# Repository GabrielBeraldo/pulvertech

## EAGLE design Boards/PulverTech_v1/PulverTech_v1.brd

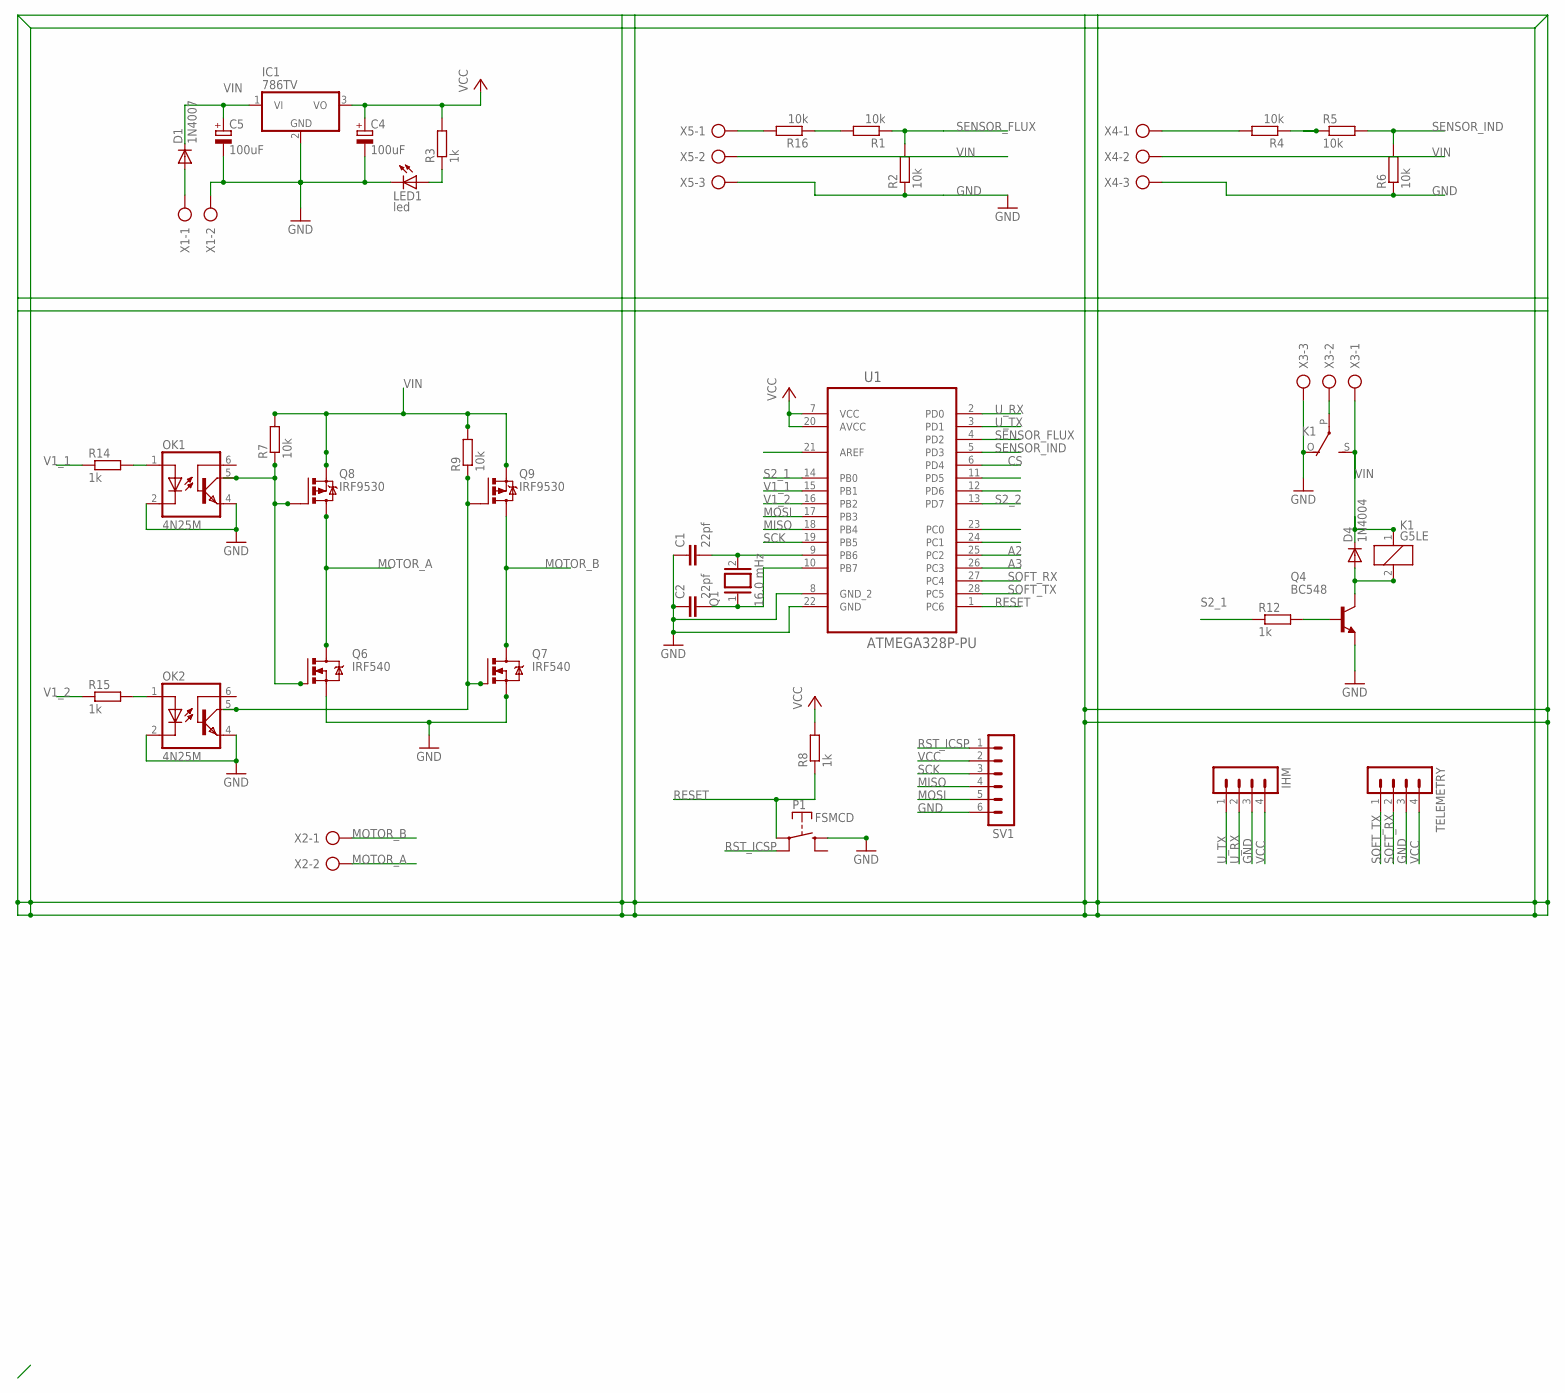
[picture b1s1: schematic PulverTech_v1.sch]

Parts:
C1, C2: 22pf; C025-025X050
C4, C5: 100uF; E2,5-5
D1: 1N4007; DO41-10
D4: 1N4004; DO41-10
IC1: 786TV; TO220V
IHM: MA04-1
K1: G5LE
LED1: led; LED3MM
OK1, OK2: 4N25M; DIL06
P1: FSMCD
Q1: 16.0 mHz; QS
Q4: BC548; TO92-EBC
Q6, Q7: IRF540; TO220BV
Q8, Q9: IRF9530; TO220BV
R1, R2, R4, R5, R6, R7, R9, R16: 10k; 0204/7
R3, R8, R12, R14, R15: 1k; 0204/7
SV1: MA06-1
TELEMETRY: MA04-1
U1: ATMEGA328P-PU; DIP254P762X457-28
X1, X2: AK500/2
X3, X4, X5: AK500/3

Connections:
A2: U1.25 (PC2)
A3: U1.26 (PC3)
CS: U1.6 (PD4)
GND: C1.1, C2.1, C4.-, C5.-, IC1.2 (GND), IHM.3, K1.O, LED1.K (C), OK1.2 (C), OK1.4 (EMI), OK2.2 (C), OK2.4 (EMI), P1.P$3 (S), Q4.E, Q6.S, Q7.S, R2.1, R6.1, SV1.6, TELEMETRY.3, U1.8 (GND_2), U1.22 (GND), X1.2, X3.3, X4.3, X5.3
GND2: K1.P, X3.2
MISO: SV1.4, U1.18 (PB4)
MOSI: SV1.5, U1.17 (PB3)
MOTOR_A: Q6.D, Q8.D, X2.2
MOTOR_B: Q7.D, Q9.D, X2.1
unnamed: C1.2, Q1.2, U1.9 (PB6)
unnamed: C2.2, Q1.1, U1.10 (PB7)
unnamed: R1.2, R16.1
unnamed: D1.A, X1.1
unnamed: R4.2, X4.1
unnamed: LED1.A, R3.1
unnamed: R16.2, X5.1
unnamed: OK1.5 (COL), Q6.G, Q8.G, R7.1
unnamed: OK1.1 (A), R14.2
unnamed: OK2.1 (A), R15.2
unnamed: R4.1, R5.1
unnamed: D4.A, K1.2, Q4.C
unnamed: Q4.B, R12.2
unnamed: OK2.5 (COL), Q7.G, Q9.G, R9.1
RESET: P1.P$1, R8.1, U1.1 (PC6)
RST_ICSP: P1.P$2, SV1.1
S2_1: R12.1, U1.14 (PB0)
S2_2: U1.13 (PD7)
SCK: SV1.3, U1.19 (PB5)
SENSOR_FLUX: R1.1, R2.2, U1.4 (PD2)
SENSOR_IND: R5.2, R6.2, U1.5 (PD3)
SOFT_RX: TELEMETRY.2, U1.27 (PC4)
SOFT_TX: TELEMETRY.1, U1.28 (PC5)
U_RX: IHM.2, U1.2 (PD0)
U_TX: IHM.1, U1.3 (PD1)
V1_1: R14.1, U1.15 (PB1)
V1_2: R15.1, U1.16 (PB2)
VCC: C4.+, IC1.3 (VO), IHM.4, R3.2, R8.2, SV1.2, TELEMETRY.4, U1.7 (VCC), U1.20 (AVCC)
VIN: C5.+, D1.C, D4.C, IC1.1 (VI), K1.1, K1.S, Q8.S, Q9.S, R7.2, R9.2, X3.1, X4.2, X5.2

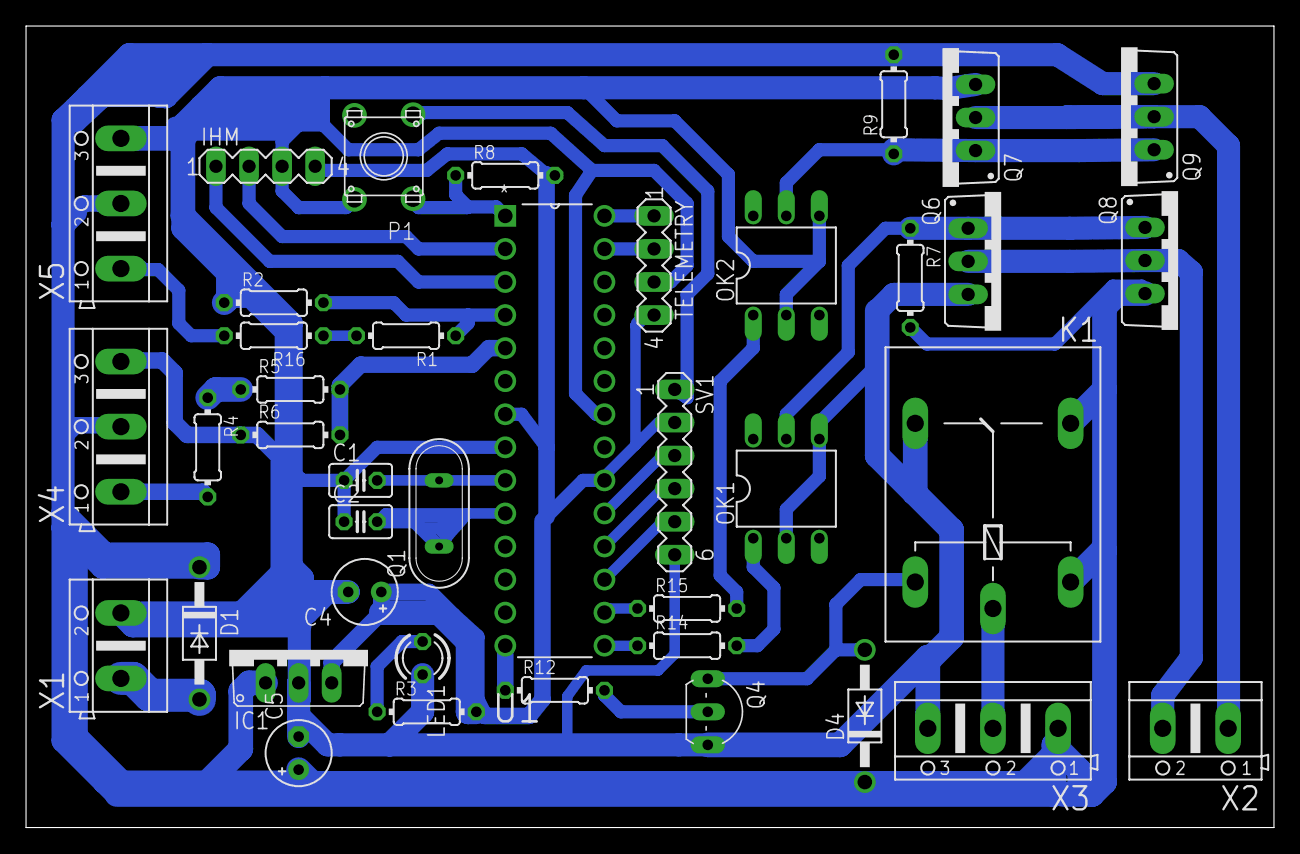
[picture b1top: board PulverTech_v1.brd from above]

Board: 2 copper layers, 95.9 x 61.6 mm, 40 parts (0 on the bottom side), 34 nets.

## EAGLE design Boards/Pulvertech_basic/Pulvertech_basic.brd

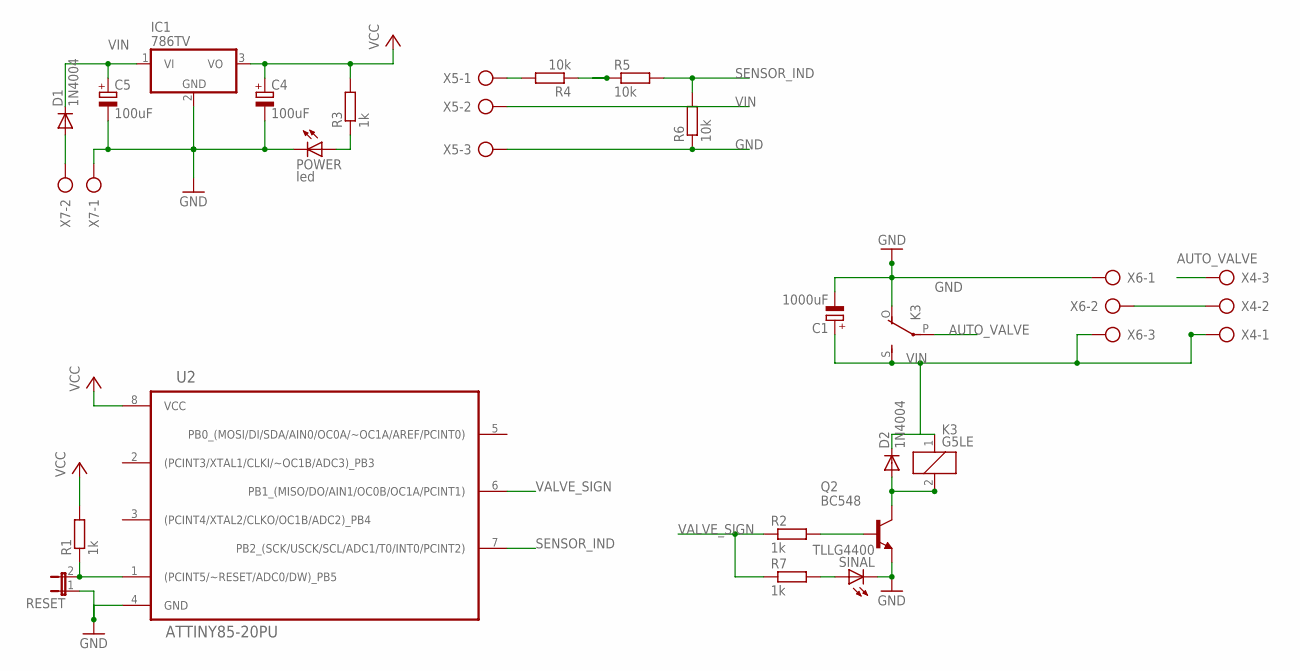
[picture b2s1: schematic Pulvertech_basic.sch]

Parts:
C1: 1000uF; E5-10,5
C4, C5: 100uF; E2,5-5
D1, D2: 1N4004; DO41-10
IC1: 786TV; TO220V
K3: G5LE
POWER: led; LED3MM
Q2: BC548; TO92-EBC
R1, R2, R3, R7: 1k; 0204/7
R4, R5, R6: 10k; 0204/7
RESET: JP1E; JP1
SINAL: TLLG4400; LED3MM
U2: ATTINY85-20PU; DIP254P762X533-8
X4, X5, X6: AK500/3
X7: AK500/2

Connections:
AUTO_VALVE: K3.P, X4.3
GND: C1.-, C4.-, C5.-, IC1.2 (GND), K3.O, POWER.K (C), Q2.E, R6.1, RESET.1, SINAL.K (C), U2.4 (GND), X5.3, X6.1, X7.1
unnamed: R1.1, RESET.2, U2.1 ((PCINT5/~RESET/ADC0/DW)_PB5)
unnamed: R4.2, X5.1
unnamed: Q2.B, R2.2
unnamed: X4.2, X6.2
unnamed: D1.A, X7.2
unnamed: R7.2, SINAL.A
unnamed: POWER.A, R3.1
unnamed: D2.A, K3.2, Q2.C
unnamed: R4.1, R5.1
SENSOR_IND: R5.2, R6.2, U2.7 (PB2_(SCK/USCK/SCL/ADC1/T0/INT0/PCINT2))
VALVE_SIGN: R2.1, R7.1, U2.6 (PB1_(MISO/DO/AIN1/OC0B/OC1A/PCINT1))
VCC: C4.+, IC1.3 (VO), R1.2, R3.2, U2.8 (VCC)
VIN: C1.+, C5.+, D1.C, D2.C, IC1.1 (VI), K3.1, K3.S, X4.1, X5.2, X6.3

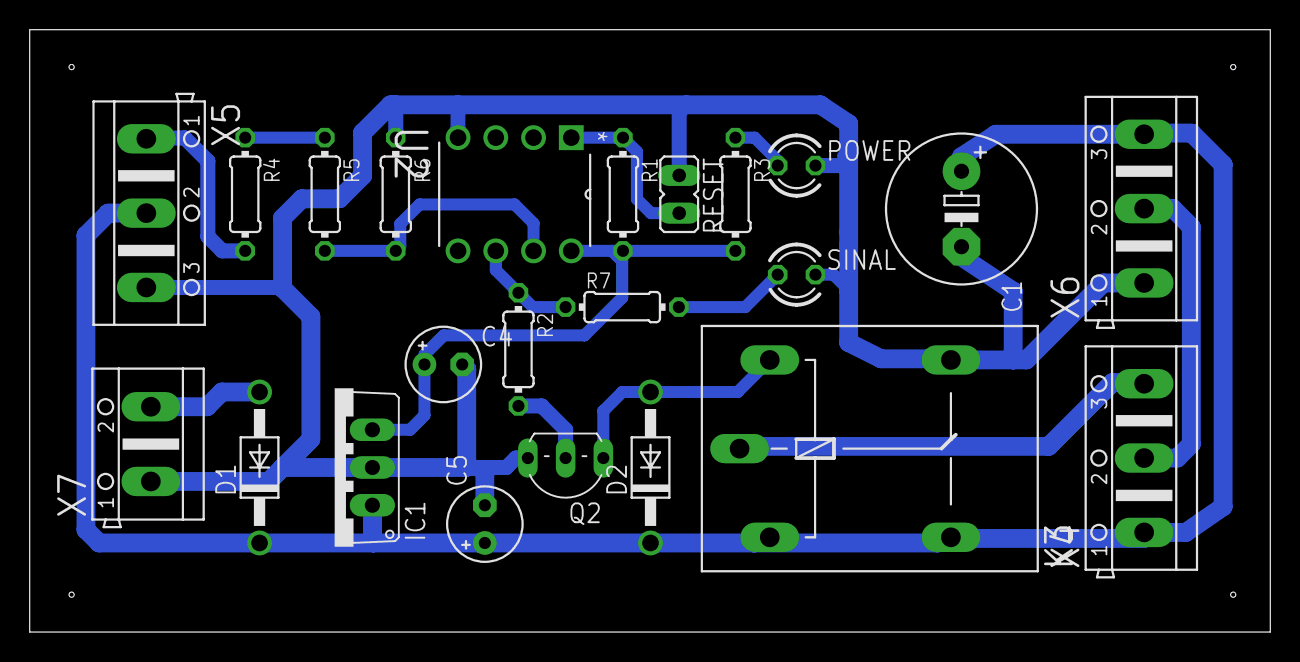
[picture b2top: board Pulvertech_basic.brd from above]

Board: 2 copper layers, 83.5 x 40.5 mm, 23 parts (0 on the bottom side), 15 nets.

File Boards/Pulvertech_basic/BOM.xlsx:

Part | Value | Device | Package | Description
C1 | 1000uF | CPOL-EUE5-10.5 | E5-10,5 | POLARIZED CAPACITOR, European symbol
C4 | 100uF | CPOL-EUE2.5-5 | E2,5-5 | POLARIZED CAPACITOR, European symbol
C5 | 100uF | CPOL-EUE2.5-5 | E2,5-5 | POLARIZED CAPACITOR, European symbol
D1 | 1N4004 | 1N4004 | DO41-10 | DIODE
D2 | 1N4004 | 1N4004 | DO41-10 | DIODE
IC1 | 786TV | 786TV | TO220V | Positive VOLTAGE REGULATOR
K3 | G5LE | G5LE | G5LE | RELAY
POWER | led | LED3MM | LED3MM | LED
Q2 | BC548 | BC548 | TO92-EBC | NPN Transistor
R1 | 1k | R0204/7 | 0204/7 | RESISTOR, European symbol
R2 | 1k | R0204/7 | 0204/7 | RESISTOR, European symbol
R3 | 1k | R0204/7 | 0204/7 | RESISTOR, European symbol
R4 | 10k | R0204/7 | 0204/7 | RESISTOR, European symbol
R5 | 10k | R0204/7 | 0204/7 | RESISTOR, European symbol
R6 | 10k | R0204/7 | 0204/7 | RESISTOR, European symbol
R7 | 1k | R0204/7 | 0204/7 | RESISTOR, European symbol
RESET |  | JP1E | JP1 | JUMPER
SINAL | TLLG4400 | TLLG4400 | LED3MM | Low Current (2mA) LED 3 mm Tinted Diffused Package color GREEN
U2 | ATTINY85-20PU | ATTINY85-20PU | DIP254P762X533-8 | 8-bit Microcontroller with In-System Programmable Flash
X4 |  | AK500/3 | AK500/3 | CONNECTOR
X5 |  | AK500/3 | AK500/3 | CONNECTOR
X6 |  | AK500/3 | AK500/3 | CONNECTOR
X7 |  | AK500/2 | AK500/2 | CONNECTOR

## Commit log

2018-02-22 summ
    first commit
2018-03-01 New board integrated
    removed sd card support
    add filters on speed next values
2018-03-01 Boards add
    some organization
2018-03-03 update
    corrections and updates
2018-03-20 SerialCommand Class implementation
2018-03-21 Class implementations
2018-03-29 add aquisition features
2018-03-30 add programmer
2018-03-30 Auto stash before rebase of "origin/master"
    GitKraken test
2018-03-30 GitKraken Test
    GitKraken test
2018-03-31 .cpp now
2018-07-19 update for manufactoring
2018-07-21 updates for manufactoring
2018-07-30 Add optocouplers, changed sensor input for flux and minor changes
2019-06-24 *updates upload
2019-11-14 final project updates
2020-08-11 nextion implementation git update
